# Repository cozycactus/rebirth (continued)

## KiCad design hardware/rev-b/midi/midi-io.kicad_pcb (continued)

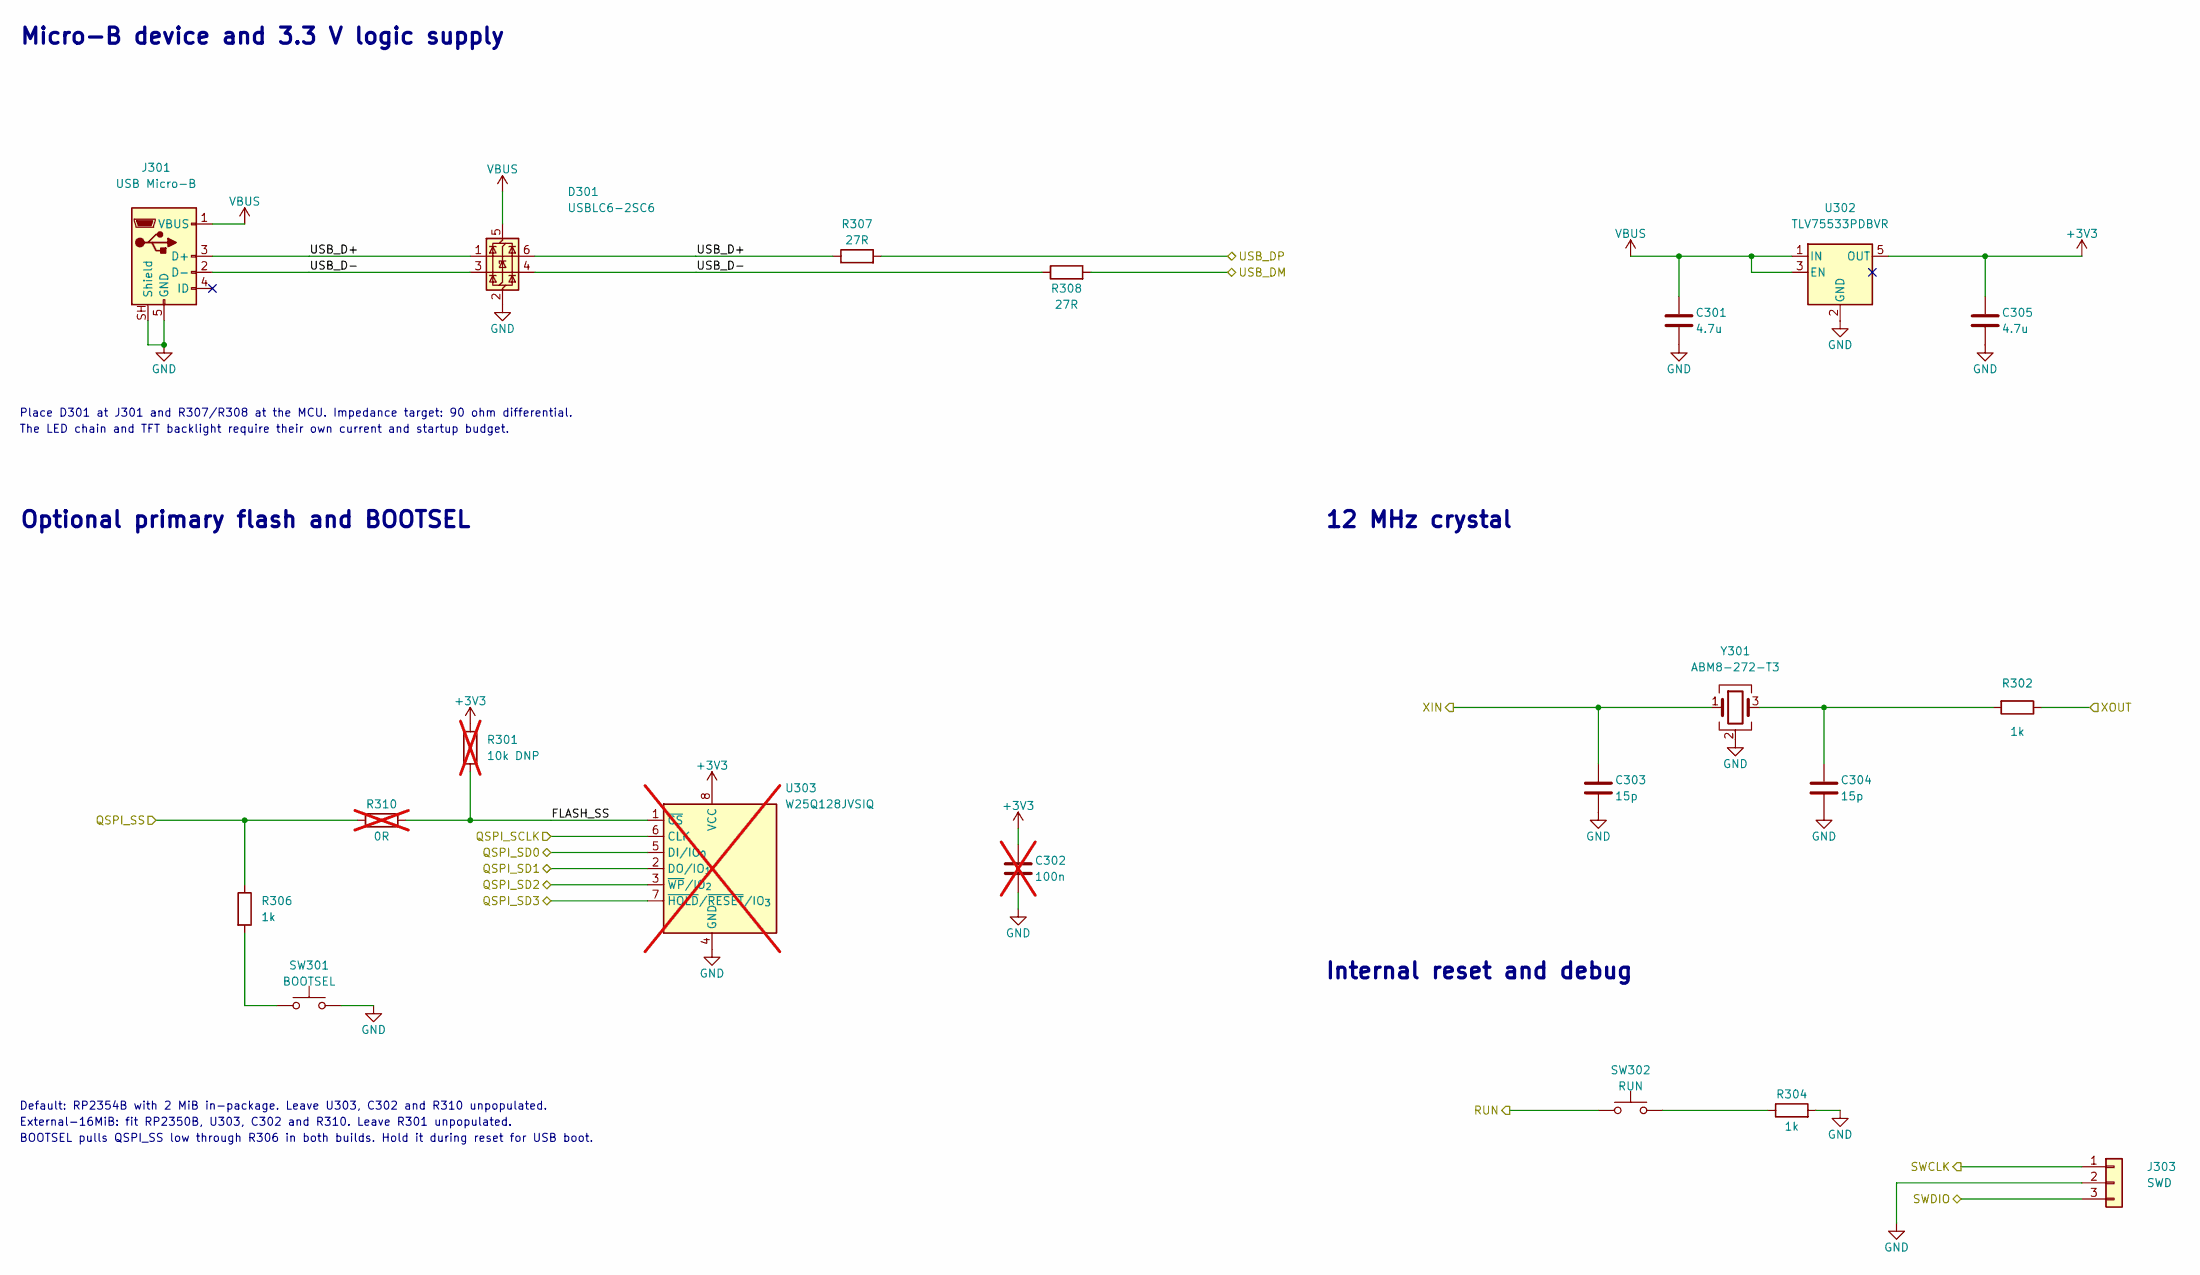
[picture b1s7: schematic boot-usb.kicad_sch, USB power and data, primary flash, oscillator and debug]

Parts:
C301, C305: 4.7u; C_0805_2012Metric; Rating 10 V X7R
C302: 100n; C_0402_1005Metric; not fitted
C303, C304: 15p; C_0402_1005Metric
D301: USBLC6-2SC6; SOT-23-6
J301: USB Micro-B; USB_Micro-B_Amphenol_10104110_Horizontal; MPN 10104110-0001LF
J303: SWD; PinHeader_1x03_P2.54mm_Vertical
R301: 10k DNP; R_0402_1005Metric; not fitted
R302, R304, R306: 1k; R_0402_1005Metric
R307, R308: 27R; R_0402_1005Metric
R310: 0R; R_0402_1005Metric; not fitted
SW301: BOOTSEL; SW_Push_1P1T_NO_Vertical_Wuerth_434133025816
SW302: RUN; SW_Push_1P1T_NO_Vertical_Wuerth_434133025816
U302: TLV75533PDBVR; SOT-23-5
U303: W25Q128JVSIQ; SOIC-8_5.3x5.3mm_P1.27mm; MPN W25Q128JVSIQ; not fitted
Y301: ABM8-272-T3; Crystal_SMD_3225-4Pin_3.2x2.5mm

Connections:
+3V3: C302.1, C305.1, R301.1, U302.5 (OUT), U303.8 (VCC); also elsewhere on the board
/QSPI_SCLK: U303.6 (CLK); also elsewhere on the board
/QSPI_SD0: U303.5 (DI/IO_{0}); also elsewhere on the board
/QSPI_SD1: U303.2 (DO/IO_{1}); also elsewhere on the board
/QSPI_SD2: U303.3 (~WP/IO_{2}); also elsewhere on the board
/QSPI_SD3: U303.7 (~HOLD/~RESET/IO_{3}); also elsewhere on the board
/QSPI_SS: R306.1, R310.1; also elsewhere on the board
/RUN: SW302.1; also elsewhere on the board
/SWCLK: J303.1; also elsewhere on the board
/SWDIO: J303.3; also elsewhere on the board
/USB, clock and storage/FLASH_SS: R301.2, R310.2, U303.1 (~CS)
/USB, clock and storage/USB_D+: D301.1 (I/O1), D301.6 (I/O1), J301.3 (D+), R307.1
/USB, clock and storage/USB_D-: D301.3 (I/O2), D301.4 (I/O2), J301.2 (D-), R308.1
/USB_DM: R308.2; also elsewhere on the board
/USB_DP: R307.2; also elsewhere on the board
/XIN: C303.1, Y301.1; also elsewhere on the board
/XOUT: R302.1; also elsewhere on the board
GND: C301.2, C302.2, C303.2, C304.2, C305.2, D301.2 (GND), J301.5 (GND), J301.SH (Shield), J303.2, R304.2, SW301.2, U302.2 (GND), U303.4 (GND), Y301.2 (G), Y301.4 (G); also elsewhere on the board
unnamed: C304.1, R302.2, Y301.3
unnamed: R304.1, SW302.2
unnamed: R306.2, SW301.1
VBUS: C301.1, D301.5 (VBUS), J301.1 (VBUS), U302.1 (IN), U302.3 (EN); also elsewhere on the board

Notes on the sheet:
Micro-B device and 3.3 V logic supply
Place D301 at J301 and R307/R308 at the MCU. Impedance target: 90 ohm differential.
The LED chain and TFT backlight require their own current and startup budget.
Optional primary flash and BOOTSEL
Default: RP2354B with 2 MiB in-package. Leave U303, C302 and R310 unpopulated.
External-16MiB: fit RP2350B, U303, C302 and R310. Leave R301 unpopulated.
BOOTSEL pulls QSPI_SS low through R306 in both builds. Hold it during reset for USB boot.
12 MHz crystal
Internal reset and debug

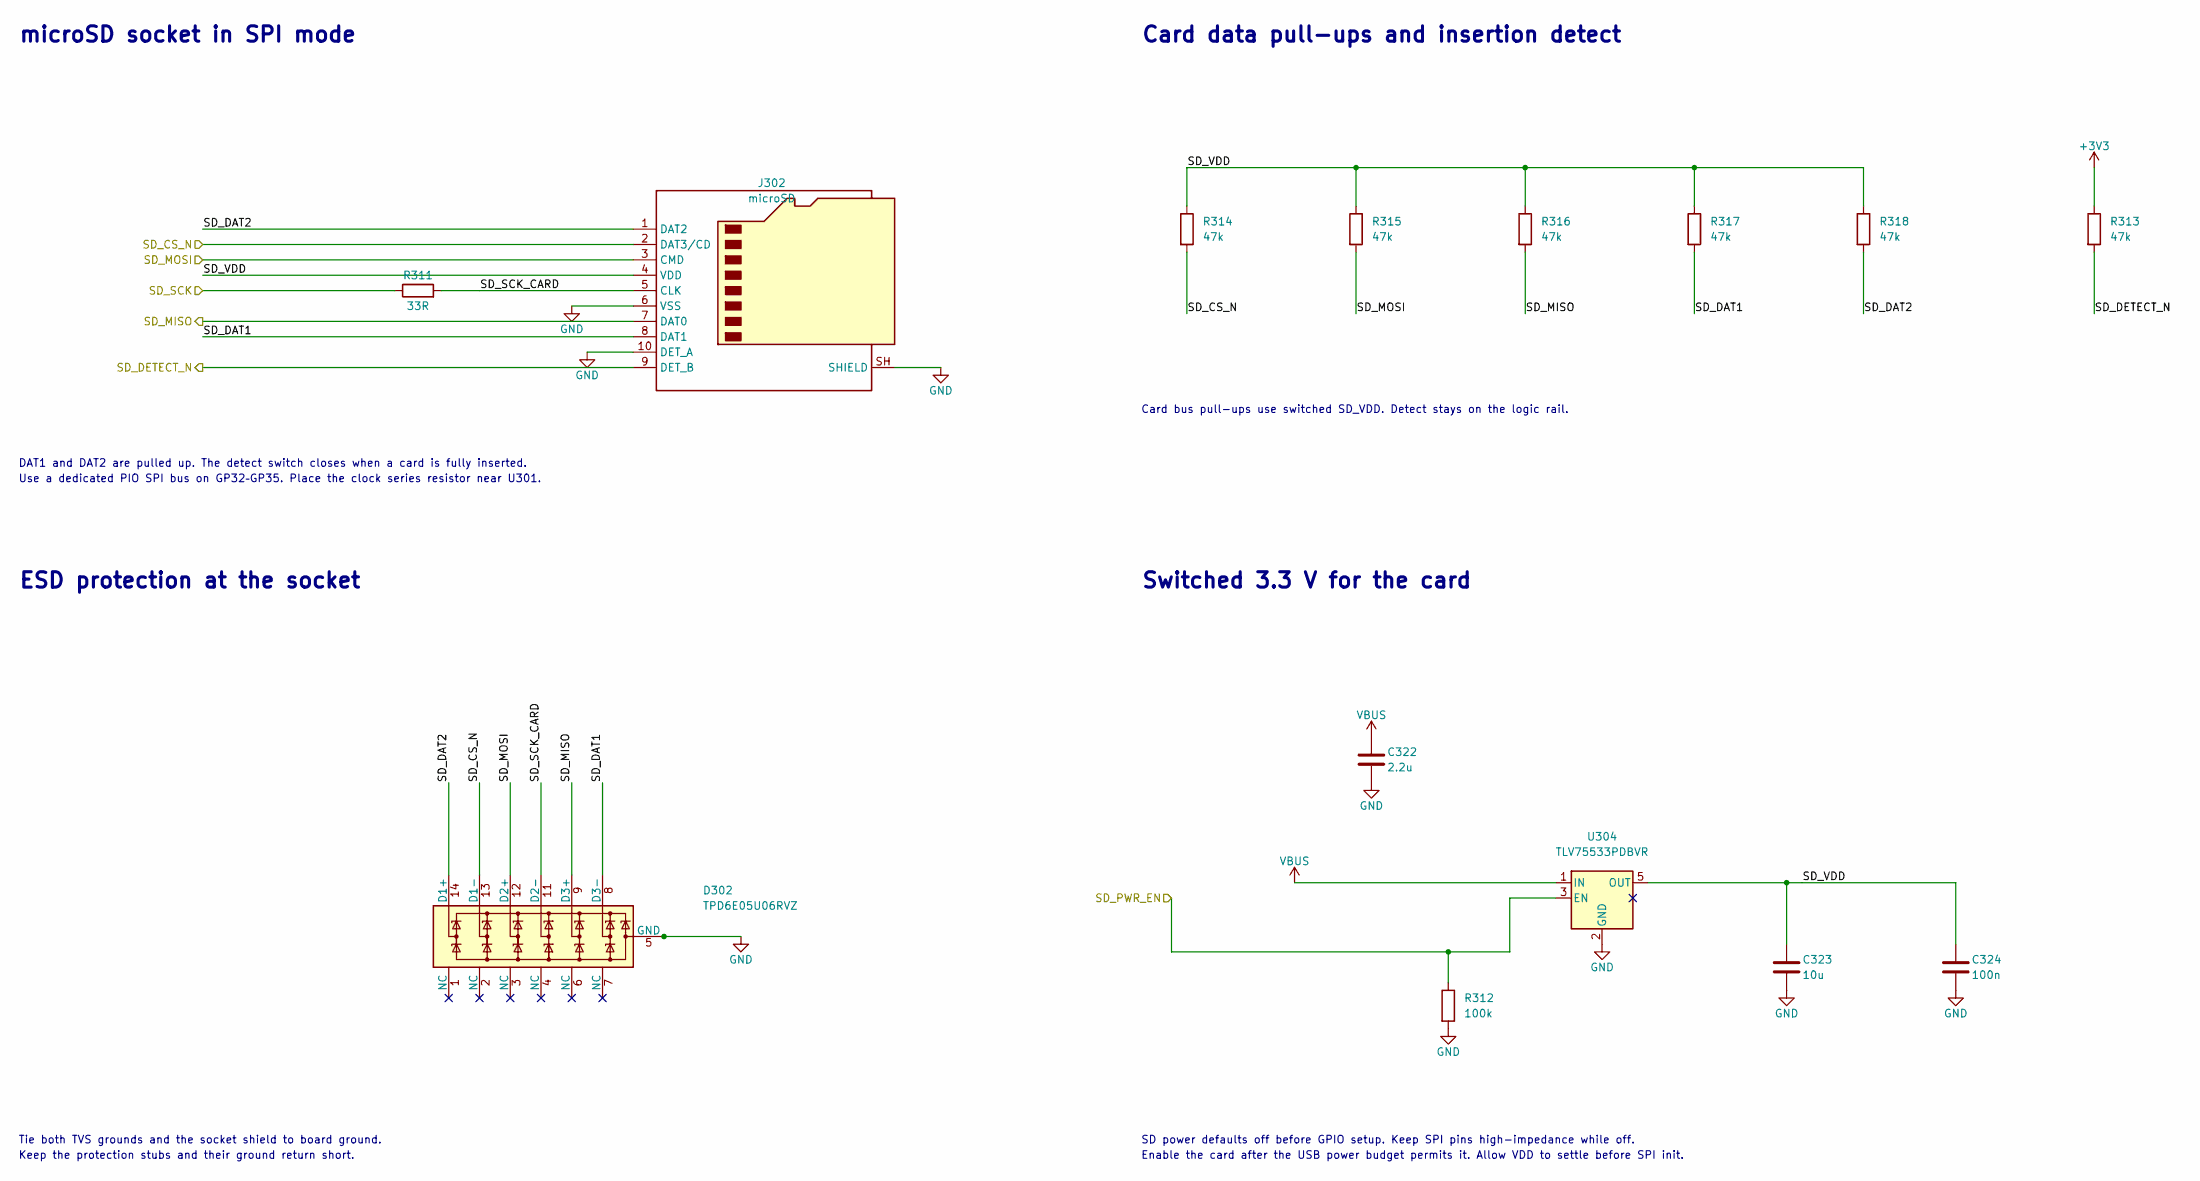
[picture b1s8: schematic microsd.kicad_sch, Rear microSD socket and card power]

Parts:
C322: 2.2u; C_0805_2012Metric; Rating 10 V X7R
C323: 10u; C_0805_2012Metric; Rating 10 V X7R
C324: 100n; C_0402_1005Metric; Rating 10 V X7R
D302: TPD6E05U06RVZ; Texas_R-PUSON-N14; MPN TPD6E05U06RVZR
J302: microSD; microSD_HC_Hirose_DM3AT-SF-PEJM5; MPN DM3AT-SF-PEJM5
R311: 33R; R_0402_1005Metric
R312: 100k; R_0402_1005Metric
R313, R314, R315, R316, R317, R318: 47k; R_0402_1005Metric
U304: TLV75533PDBVR; SOT-23-5

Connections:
+3V3: R313.1; also elsewhere on the board
/SD_CS_N: D302.13 (D1-), J302.2 (DAT3/CD), R314.2; also elsewhere on the board
/SD_DETECT_N: J302.9 (DET_B), R313.2; also elsewhere on the board
/SD_MISO: D302.9 (D3+), J302.7 (DAT0), R316.2; also elsewhere on the board
/SD_MOSI: D302.12 (D2+), J302.3 (CMD), R315.2; also elsewhere on the board
/SD_PWR_EN: R312.1, U304.3 (EN); also elsewhere on the board
/SD_SCK: R311.1; also elsewhere on the board
/microSD/SD_DAT1: D302.8 (D3-), J302.8 (DAT1), R317.2
/microSD/SD_DAT2: D302.14 (D1+), J302.1 (DAT2), R318.2
/microSD/SD_SCK_CARD: D302.11 (D2-), J302.5 (CLK), R311.2
/microSD/SD_VDD: C323.1, C324.1, J302.4 (VDD), R314.1, R315.1, R316.1, R317.1, R318.1, U304.5 (OUT)
GND: C322.2, C323.2, C324.2, D302.5 (GND), D302.10 (GND), J302.6 (VSS), J302.10 (DET_A), J302.SH (SHIELD), R312.2, U304.2 (GND); also elsewhere on the board
VBUS: C322.1, U304.1 (IN); also elsewhere on the board

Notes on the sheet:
microSD socket in SPI mode
DAT1 and DAT2 are pulled up. The detect switch closes when a card is fully inserted.
Use a dedicated PIO SPI bus on GP32–GP35. Place the clock series resistor near U301.
Card data pull-ups and insertion detect
Card bus pull-ups use switched SD_VDD. Detect stays on the logic rail.
ESD protection at the socket
Tie both TVS grounds and the socket shield to board ground.
Keep the protection stubs and their ground return short.
Switched 3.3 V for the card
SD power defaults off before GPIO setup. Keep SPI pins high-impedance while off.
Enable the card after the USB power budget permits it. Allow VDD to settle before SPI init.

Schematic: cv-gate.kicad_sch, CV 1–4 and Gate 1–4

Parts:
C501, C502, C504, C505, C507: 100n; C_0603_1608Metric
C506: 1u; C_0805_2012Metric
C511, C512, C513, C514: 1n C0G; C_0603_1608Metric
D501, D502, D503, D504, D505, D506, D507, D508: PESD5V0S1BA; D_SOD-323
J501, J502, J503, J504, J505, J506, J507, J508: 3.5mm TRS; Jack_3.5mm_CUI_SJ1-3533NG_Horizontal
R511, R512, R513, R514, R541, R542, R543, R544: 1k; R_0603_1608Metric
R515, R516, R517, R518, R531, R532, R533, R534, R551, R552, R553, R554: 100k; R_0603_1608Metric
R521, R522, R523, R524, R567, R568, R571, R572, R573: 10k; R_0603_1608Metric
R561, R562, R563, R564: 33R; R_0603_1608Metric
R565, R566, R569, R570: 47k; R_0603_1608Metric
U501, U502: MCP4822; SOIC-8_3.9x4.9mm_P1.27mm
U503: MCP6004; SOIC-14_3.9x8.7mm_P1.27mm
U504: SN74LVC8T245PWR; TSSOP-24_4.4x7.8mm_P0.65mm; MPN SN74LVC8T245PWR

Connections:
+3V3: C505.1, R567.1, R568.1, R573.1, U504.1 (V_{CCA}), U504.2 (DIR); also elsewhere on the board
/CV and Gate/CV1: D501.1 (A1), J501.T, R511.2, R521.2
/CV and Gate/CV1_DAC: R515.1, U501.8 (VA), U503.3 (+)
/CV and Gate/CV2: D502.1 (A1), J502.T, R512.2, R522.2
/CV and Gate/CV2_DAC: R516.1, U501.6 (VB), U503.5 (+)
/CV and Gate/CV3: D503.1 (A1), J503.T, R513.2, R523.2
/CV and Gate/CV3_DAC: R517.1, U502.8 (VA), U503.10 (+)
/CV and Gate/CV4: D504.1 (A1), J504.T, R514.2, R524.2
/CV and Gate/CV4_DAC: R518.1, U502.6 (VB), U503.12 (+)
/CV and Gate/DAC_CS1_N_T: R563.2, R571.2, U501.2 (~CS)
/CV and Gate/DAC_CS2_N_T: R564.2, R572.2, U502.2 (~CS)
/CV and Gate/DAC_MOSI_T: R562.2, R570.1, U501.4 (SDI), U502.4 (SDI)
/CV and Gate/DAC_SCK_T: R561.2, R569.1, U501.3 (SCK), U502.3 (SCK)
/CV and Gate/GATE1_BUF: R541.1, U504.17 (B5)
/CV and Gate/GATE1_OUT: D505.1 (A1), J505.T, R541.2, R551.1
/CV and Gate/GATE2_BUF: R542.1, U504.16 (B6)
/CV and Gate/GATE2_OUT: D506.1 (A1), J506.T, R542.2, R552.1
/CV and Gate/GATE3_BUF: R543.1, U504.15 (B7)
/CV and Gate/GATE3_OUT: D507.1 (A1), J507.T, R543.2, R553.1
/CV and Gate/GATE4_BUF: R544.1, U504.14 (B8)
/CV and Gate/GATE4_OUT: D508.1 (A1), J508.T, R544.2, R554.1
/CV_ENABLE_N: R573.2, U504.22 (~OE); also elsewhere on the board
/DAC_CS1_N: R567.2, U504.5 (A3); also elsewhere on the board
/DAC_CS2_N: R568.2, U504.6 (A4); also elsewhere on the board
/DAC_MOSI: R566.1, U504.4 (A2); also elsewhere on the board
/DAC_SCK: R565.1, U504.3 (A1); also elsewhere on the board
/GATE1: R531.1, U504.7 (A5); also elsewhere on the board
/GATE2: R532.1, U504.8 (A6); also elsewhere on the board
/GATE3: R533.1, U504.9 (A7); also elsewhere on the board
/GATE4: R534.1, U504.10 (A8); also elsewhere on the board
GND: C501.2, C502.2, C504.2, C505.2, C506.2, C507.2, D501.2 (A2), D502.2 (A2), D503.2 (A2), D504.2 (A2), D505.2 (A2), D506.2 (A2), D507.2 (A2), D508.2 (A2), J501.S, J502.S, J503.S, J504.S, J505.S, J506.S, J507.S, J508.S, R515.2, R516.2, R517.2, R518.2, R531.2, R532.2, R533.2, R534.2, R551.2, R552.2, R553.2, R554.2, R565.2, R566.2, R569.2, R570.2, U501.5 (~LDAC), U501.7 (Vss), U502.5 (~LDAC), U502.7 (Vss), U503.11 (V-), U504.11 (GND), U504.12 (GND), U504.13 (GND); also elsewhere on the board
unnamed: C511.2, R511.1, U503.1
unnamed: C512.2, R512.1, U503.7
unnamed: C513.2, R513.1, U503.8
unnamed: C514.2, R514.1, U503.14
unnamed: C511.1, R521.1, U503.2 (-)
unnamed: C512.1, R522.1, U503.6 (-)
unnamed: C513.1, R523.1, U503.9 (-)
unnamed: C514.1, R524.1, U503.13 (-)
unnamed: R561.1, U504.21 (B1)
unnamed: R562.1, U504.20 (B2)
unnamed: R563.1, U504.19 (B3)
unnamed: R564.1, U504.18 (B4)
VBUS: C501.1, C502.1, C504.1, C506.1, C507.1, R571.1, R572.1, U501.1 (Vdd), U502.1 (Vdd), U503.4 (V+), U504.23 (V_{CCB}), U504.24 (V_{CCB}); also elsewhere on the board

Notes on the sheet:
CV/Gate level translation
DIR is high. A takes 3.3 V logic, B drives the VBUS domain.
OE stays high until firmware sets chip selects high and the four gates low.
Place the 33 ohm SPI series resistors close to U504.
Reset levels
Four pitch outputs, 1 V/octave
MCP4822 at gain 2x on VBUS. Nominal 1 mV/LSB at the jack.
At 4.096 V full scale, allow supply and buffer headroom under load.
Measure slope and offset at the jacks with the connected synth.
CV 1
CV 2
CV 3
CV 4
MCP6004 buffers. R511–R514 are inside the DC feedback loop.
C511–C514 close local feedback at high frequency.
D501–D508 are rear-jack TVS diodes.
Four active-high Gate outputs
GATE 1
GATE 2
GATE 3
GATE 4
The jacks are held low while OE is high.
Use the tip and sleeve of a TS cable. Ring is open.
Check the high Gate level and CV settling under load.

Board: 2 copper layers, 187 parts (0 on the bottom side), 114 nets, no tracks yet.

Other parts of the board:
H1, H2, H3, H4, H5, H6, H7: MountingHole_3.2mm_M3_Pad_Via
J1101: IDC 2x13, wire order; IDC-Header_2x13_P2.54mm_Horizontal

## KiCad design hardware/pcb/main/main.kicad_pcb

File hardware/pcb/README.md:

# PCB: main board and panel board

Two KiCad 10 projects, one per board, generated from the schematic
(`hardware/schematic/`, its README first):

| Board | Project | Size | Contents |
| --- | --- | --- | --- |
| Panel board | `panel/panel.kicad_pro` | 248 x 251 mm | 8x8 pads, 8 SCENE, 8 MUTE, PLAY (81 MX switches), 82 SK6812MINI-E, 80 BAT54J, 16 step buttons and LEDs, 5 MCP23017, encoders, OLED socket, LED data buffer, cable header J1201 |
| Main board | `main/main.kicad_pro` | 244 x 57.5 mm | Raspberry Pi Pico, LED-rail switch U201, MIDI OUT/IN, 2 x MCP4822 + MCP6004, gate buffer, 8 jacks, 2 DIN-5, cable header J1101 |

The two boards are joined by a 26-wire IDC ribbon, J1101 pin n to J1201 pin n.

## Decisions (owner, 2026-11-16)

| Question | Decision |
| --- | --- |
| One board or two | Two: panel board under the top plate, main board on the case floor at the rear wall |
| Copper layers | 2 on both boards, 1.6 mm FR4, 1 oz |
| Fab and assembly | JLCPCB, their SMT assembly with LCSC parts; through-hole parts soldered by hand |
| Pads | MX-type switches soldered to the panel board, translucent 17 mm keycaps through windows in the 2 mm aluminium top plate, board on 15 mm standoffs |
| LED rail enable | JP201: EN = +3V3 as designed, GPIO 7 by moving a solder jumper |
| Jack protection | 5 V TVS on all eight jacks |
| Case height | 28 mm at the front, 50 mm at the rear (mockup: 20/45 mm) |

The board plan was reviewed independently (Codex, DeepSeek, Grok; Gemini could not run) before
layout. What came out of it is in the schematic README (decisions 12-14) and below.

## Regenerating

The boards are generated, like the schematic. With KiCad 10 installed:

```bash
python3 hardware/schematic/gen/build.py --check          # schematics of all three projects
PY=/Applications/KiCad/KiCad.app/Contents/Frameworks/Python.framework/Versions/Current/bin/python3
$PY hardware/pcb/gen/build_pcb.py panel place            # footprints, outline, holes, regular routing
$PY hardware/pcb/gen/build_pcb.py panel maze             # grid router for the rest (panel)
$PY hardware/pcb/gen/build_pcb.py panel finish           # GND pours, stitching vias, DRC + parity
```

For the main board: `place`, then
`FREEROUTING_JAR=/path/to/freerouting-2.4.1.jar $PY hardware/pcb/gen/build_pcb.py main route`,
then `maze` and `finish`. `place` overwrites the board file; `route` hands the unrouted
connections to Freerouting (GND is left out, it is poured); `maze` joins what is still open
with the grid router in `gen/maze.py`; `finish` adds the GND pours on both layers and stitching
vias, joins GND islands, refills and runs `kicad-cli pcb drc --schematic-parity`. Run `finish`
again until the DRC summary it prints stops changing (two or three times). The panel takes
about half an hour, the main board a few minutes. Placement is
in `gen/panel.py` and `gen/mainboard.py`, the panel geometry in `gen/geometry.py` (from the
Blender mockup `hardware/panel/build_panel.py`).

## Mechanics (case frame: x to the right, y toward the rear wall, z up)

The Blender model `hardware/panel/build_internals.py` shows all of this and animates it
(scene "Sequencer Internals": the plate and caps lift off, the lid with the panel board opens).

- **Stack under the top plate.** Plate 2 mm; panel board top 15 mm below the plate's underside on
  M3 standoffs. Cherry MX: housing top 11.6 mm, stem top 15.2 mm above the board (MX2A datasheet:
  18.5 mm total with 3.3 mm pins); a DSA-height cap reaches ~20 mm, ~3 mm above the plate, and
  goes ~1 mm below the plate surface at full travel. Plate windows: caps + 0.8 mm. Change the
  standoffs with the keycap profile.
- **Case height** 28 mm at the front, 50 mm at the rear (tilt 4.7 deg). At the front edge the
  panel board's underside is ~12 mm above the 3 mm floor; at the rear ~2 mm stay between the
  DIN sockets and the panel board.
- **Panel board holes** (17 x M3, plated, on GND) sit around the grid block, between the step
  groups and beside the top strip; none inside the 8x8 grid (the caps leave no room for a
  standoff). Centre deflection of the 1.6 mm board between the supports is a few tenths of a
  millimetre for a 10 N press; if the grid feels soft, add a non-conductive support from the
  case floor under the grid centre. The aluminium plate is grounded through the standoffs only
  if it is bare or chromated at the screw faces (anodising insulates): use toothed washers or
  a ground tab and check < 1 ohm from the plate to GND.
- **Top strip.** EC11 encoders need a ~30 mm shaft from the board (the KiCad footprint name
  says H20mm; the pinout is the same) and pass the plate without a nut; the OLED module sits on
  ~11 mm spacers so the glass is just under the 57 x 29 mm window, plugged into the 7-pin
  socket J601 at its top edge (check the module's header position and pin order before
  ordering, or join them with a short cable). BEAT (D982) lights through a light pipe; the
  step buttons are tall 6 x 6 tactiles (~15 mm) with caps, the step LEDs stand on long legs up
  to Ø4 mm plate holes (sleeve the legs: the plate is on GND).
- **Main board** on 5 mm standoffs (7 x M3, plated, on GND, one beside the DIN sockets to take
  their up-to-5-kgf plug force). The Pico's edge is flush with the board's rear edge, so its
  micro-USB receptacle sits ~2 mm inside the 3 mm rear wall: thin the wall around the USB
  opening to ~1 mm, or use a short panel-mount extension. The jacks (CUI SJ1-3513N, no thread)
  and the DIN-5 sockets (SDS-50J) have their faces at the board's rear edge.
- **Cable.** Both headers are right angle and open toward the front: J1201 under the panel
  board above J1101 at the main board's front edge; the ribbon leaves both plugs forward and
  folds back on itself (~100 mm). Keyed headers and keyed IDC sockets, stripe = pin 1 on both
  ends.

## Cable J1101 - J1201 (wire n = pin n)

| Pin | Net | Pin | Net |
| --- | --- | --- | --- |
| 1 | +5V_LED | 2 | +5V_LED |
| 3 | GND | 4 | LED_DATA |
| 5 | GND | 6 | OLED_SCK |
| 7 | GND | 8 | OLED_MOSI |
| 9 | OLED_DC | 10 | OLED_CS_N |
| 11 | OLED_RST_N | 12 | PLAY_N |
| 13 | +3V3 | 14 | +3V3 |
| 15 | GND | 16 | I2C_SCL |
| 17 | GND | 18 | I2C_SDA |
| 19 | ENC1_A | 20 | ENC1_B |
| 21 | ENC1_SW_N | 22 | ENC2_A |
| 23 | ENC2_B | 24 | ENC2_SW_N |
| 25 | GND | 26 | GND |

A ribbon crimped the wrong way round joins pin n to pin 27 - n: +5V_LED meets GND (U201 limits
it to ~0.3 A) and +3V3 meets +3V3; no rail reaches another rail. Ring pin 1 to pin 1 before
the first power-up anyway. Up to 306 mA flows on the two +5V_LED wires and back on seven GND
wires (well within a 28 AWG ribbon and IDC contacts).

## Panel board

- **Sides.** Every SMD part is on the bottom (B), so the board needs one SMT pass; through-hole
  parts (81 MX switches, 16 tactiles, 16 step LEDs, 2 encoders, OLED socket J601, cable header
  J1201) are hand-soldered, the switches from the top. The SK6812MINI-E are reverse mounted:
  KiCad's `LED_SK6812MINI-E_3.2x2.8mm_P1.5mm_ReverseMount` placed on B.Cu, the lens in the
  board cutout under the MX LED window, 5.08 mm from the switch centre on the side away from
  the switch pins. Their pads are 0.2-0.25 mm from that cutout; `panel.kicad_dru` allows 0.2 mm
  for them only (JLCPCB routes to 0.2 mm), the rest of the board keeps 0.25 mm. JLCPCB lists
  C5149201 as Standard PCBA only; check the reel's pin 1 against the footprint (schematic
  README, notes for the PCB step) and the bottom-side rotation in the CPL before ordering.
- **Key cell** (19.5 mm pitch, KiCad coordinates relative to the switch centre, +y toward the
  front): MX footprint origin at (+2.54, -5.08); LED at (0, +5.08); its 100 nF at (+4.6, +5.8),
  vertical; BAT54J at (+4.9, -7.6), anode toward switch pin 1. Copper: ROW line on B.Cu through
  switch pin 2 at y -2.54, COL line on F.Cu at x +7.0 with the diode cathode on a via, LED chain
  on B.Cu above the LED pads, +5V_LED bus (0.6 mm) on B.Cu at y +8.6, two GND vias per cell.
- **+5V_LED**: J1201 pins 1-2 -> 1 mm F.Cu under the header body (clear of both pin rows, so
  the cable pins can leave downward on either layer) -> via -> C984 (470 uF) -> 1 mm feed along
  the top of the grid -> 1 mm spine on F.Cu down the right side (x = 95.5) -> a via onto every
  row bus and the mute bus.
- **Expanders.** Step row: U701 (0x20) and U703 (0x24) at the left margin, U702 (0x21, LEDs) at
  the right; key scanner U801 (0x22) and U802 (0x23) at the right margin next to the ROW line
  ends. Each expander's RESET pull-up sits right of its pin 18.
- **Step row buses.** Between the step LEDs (with their 470 R underneath) and the step buttons
  is a channel ~8 mm high. B.Cu carries U702's 16 LED lines to the 470 R, F.Cu the 16 button
  lines from U701/U703, 0.5 mm pitch, both drawn by `gen/panel.py`. On both expanders one pin
  column comes out in the reverse order of the row; the LED lines solve it by leaving U702 on
  both sides (GPB7 takes F.Cu round H12), the button lines by a diagonal of vias on U701's
  right column and a B.Cu loop under the chip to a staircase of vias for its left column. They
  come down between D701 and D702. U901 (LED data buffer) and C984 sit next to J1201, so the chain starts and the LED
  current enters at the same corner.
- **Routing.** The key grid, the LED supply and the step-row buses are drawn by `gen/panel.py`;
  the rest by a grid
  router (`gen/maze.py`: A* on a 0.2 mm grid on both layers, KiCad's clearances grown into the
  grid, no vias in SMD pads or next to holes). A connection that finds no way gets a trial path
  that may cross other signal nets at a cost; only the nets it crosses are ripped up and routed
  again after it, and the best of up to eight rounds is kept. Freerouting made no progress on this board (182 of 324
  connections still open after two passes and 30 minutes). Many long runs cross the grid
  diagonally: electrically fine, tidier by hand later if wanted.

## Main board

- **Left:** the Pico U301 on 8.5 mm sockets, its USB end 0.5 mm inside the rear edge; the
  source terminations R1101-R1105 and R561-R564 right at its GPIO pins (R1106 for LED_DATA on
  the other side); U201 (LED-rail switch), C201/C202, JP201 and TP201 beside its VBUS pin.
- **J1101** in front of the Pico, opening to the front edge, so the LED supply and its return
  stay at the Pico end of the board.
- **Middle:** MIDI OUT behind J401, MIDI IN (H11L1, DIP-6) behind J402.
- **Right:** gate buffer U504 between the gate jacks, op-amp U503 between the CV jacks, the two
  DACs in front of it; the 1 k / 10 k / 1 nF network and the TVS of each channel in front of
  its jack. The DAC SPI lines (~170 mm, 33 R at the source) run along the front of the board.
- All SMD parts on the top (one SMT pass). JLCPCB's Standard PCBA asks for at least 70 mm on
  the short side: order the 57.5 mm board with edge rails, or use Economic PCBA if every part
  qualifies.
- **Routing:** Freerouting, then `gen/maze.py` for the few connections it leaves (with rip-up of
  the nets that wall a pad in). GND poured on both layers, stitched.

## Fabrication (JLCPCB)

- 2 layers, FR4 1.6 mm, 1 oz copper, ENIG preferred (fine reverse-mount LED pads; HASL works).
- Rules: routed at 0.2 mm track/space; the DRC holds 0.15 mm (JLCPCB minimum 0.127 mm), vias
  0.6/0.3 mm (power 0.8/0.4 mm), copper 0.25 mm from the outline (0.2 mm for the LED pads at
  their cutouts), hole to hole 0.5 mm.
- Fiducials: three per assembly side (panel: bottom, main: top). Mounting holes are plated
  and on GND. Reference designators of the dense parts are on the fab layers, so the
  silkscreen stays readable; the assembly drawing comes from F.Fab/B.Fab.
- Not prepared here: BOM with LCSC numbers and the CPL (the schematic has no MPNs yet).

## Verification (2026-11-16, KiCad 10.0.7)

| Check | Main board | Panel board |
| --- | --- | --- |
| `kicad-cli pcb drc --schematic-parity --severity-all` against the rules above | 0 violations, 0 unconnected, 0 parity issues | 0 violations, 0 unconnected, 0 parity issues |
| Footprints / nets on the board = schematic | 109 / 91 | 437 / 307 |
| Copper connectivity (kicad-happy `analyze_pcb.py --full`, union-find over pads, tracks, vias and fills) | every net one island | every net one island |
| kicad-happy `cross_analysis.py` | 2 info (MIDI DIN pins without ESD parts) | 0 findings |

Schematics: `python3 hardware/schematic/gen/build.py --check` gives 0 problems and 0 ERC
violations for all three projects (380 / 91 / 307 nets) and 26 of 26 cable pins matched; the
generated sheets are unchanged by the PCB work. Copper pictures: `renders/panel_copper.jpg`,
`renders/main_copper.jpg` (F.Cu pour drawn over B.Cu).

kicad-happy findings that stay, and why:

- Main, PM-002 "courtyard overhangs the board edge": J401/J402 (0.5 mm), J501-J508 (4 mm) and
  U301 (1.06 mm). On purpose: the jack and DIN faces and the Pico's USB end sit at the rear edge.
- Main, CC-002: two short MIDI_TX segments (under 3 mm together) at 0.15 mm, where Freerouting
  necked down between pins; above JLCPCB's 0.127 mm, and the line carries ~5 mA. Everything else
  is 0.2 mm or wider.
- Both, TE-001 test-point coverage (2 of 88 nets on main, none on the panel): bring-up uses the
  Pico pins, the jacks and the cable header; TP201 and TP301 are the only test points.
- Main schematic, CG-AUD "J402 has no ground pin": MIDI IN leaves pin 2 open by the MIDI spec.
- Main schematic, PU-001 "U201 EN without pull-up": EN has R203 to GND and JP201 to +3V3 (or
  GPIO 7), as designed.
- Both schematics, DS-001 / SS-001: no datasheets folder and no MPNs, so the analyzer's checks
  are consistency checks only, not checks against the parts' datasheets.

Not done here: Gerbers, drill files, BOM with LCSC numbers and the CPL; the EMC, thermal and
SPICE passes of kicad-happy; a readable-schematic lint of the regenerated sheets (it timed out
after 600 s; the sheets were checked by eye on renders). Freerouting results vary from run to
run, so a regenerated main board is not identical to the committed one; the panel's routing
comes out the same every time.

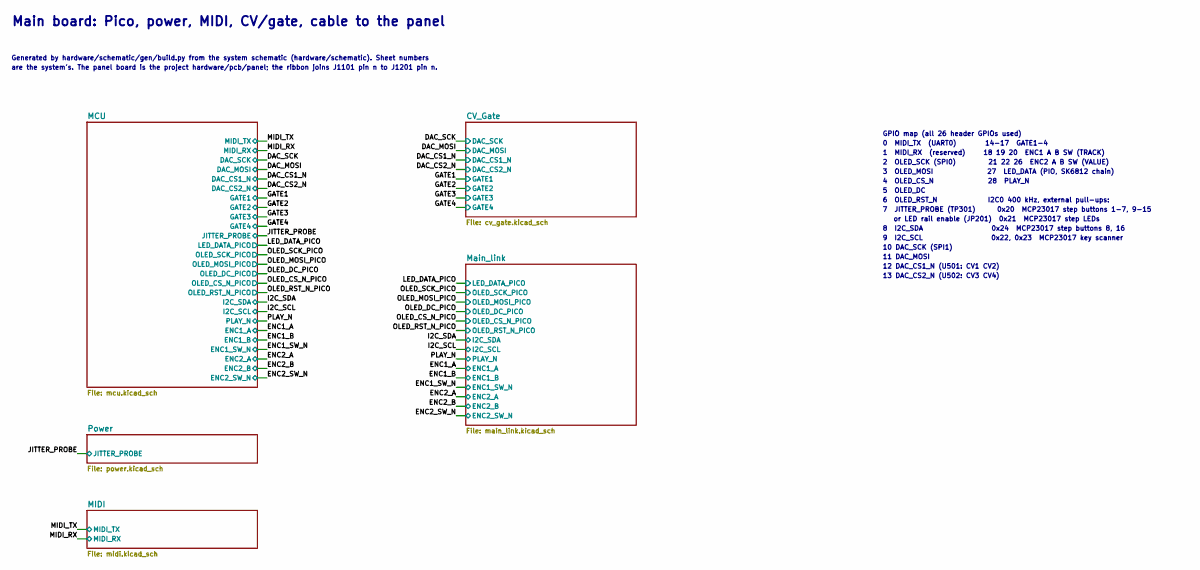
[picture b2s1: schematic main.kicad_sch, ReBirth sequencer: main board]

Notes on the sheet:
Main board: Pico, power, MIDI, CV/gate, cable to the panel
Generated by hardware/schematic/gen/build.py from the system schematic (hardware/schematic). Sheet numbers
are the system's. The panel board is the project hardware/pcb/panel; the ribbon joins J1101 pin n to J1201 pin n.
GPIO map (all 26 header GPIOs used)
0 MIDI_TX (UART0) 14-17 GATE1-4
1 MIDI_RX (reserved) 18 19 20 ENC1 A B SW (TRACK)
2 OLED_SCK (SPI0) 21 22 26 ENC2 A B SW (VALUE)
3 OLED_MOSI 27 LED_DATA (PIO, SK6812 chain)
4 OLED_CS_N 28 PLAY_N
5 OLED_DC
6 OLED_RST_N I2C0 400 kHz, external pull-ups:
7 JITTER_PROBE (TP301) 0x20 MCP23017 step buttons 1-7, 9-15
or LED rail enable (JP201) 0x21 MCP23017 step LEDs
8 I2C_SDA 0x24 MCP23017 step buttons 8, 16
9 I2C_SCL 0x22, 0x23 MCP23017 key scanner
10 DAC_SCK (SPI1)
11 DAC_MOSI
12 DAC_CS1_N (U501: CV1 CV2)
13 DAC_CS2_N (U502: CV3 CV4)

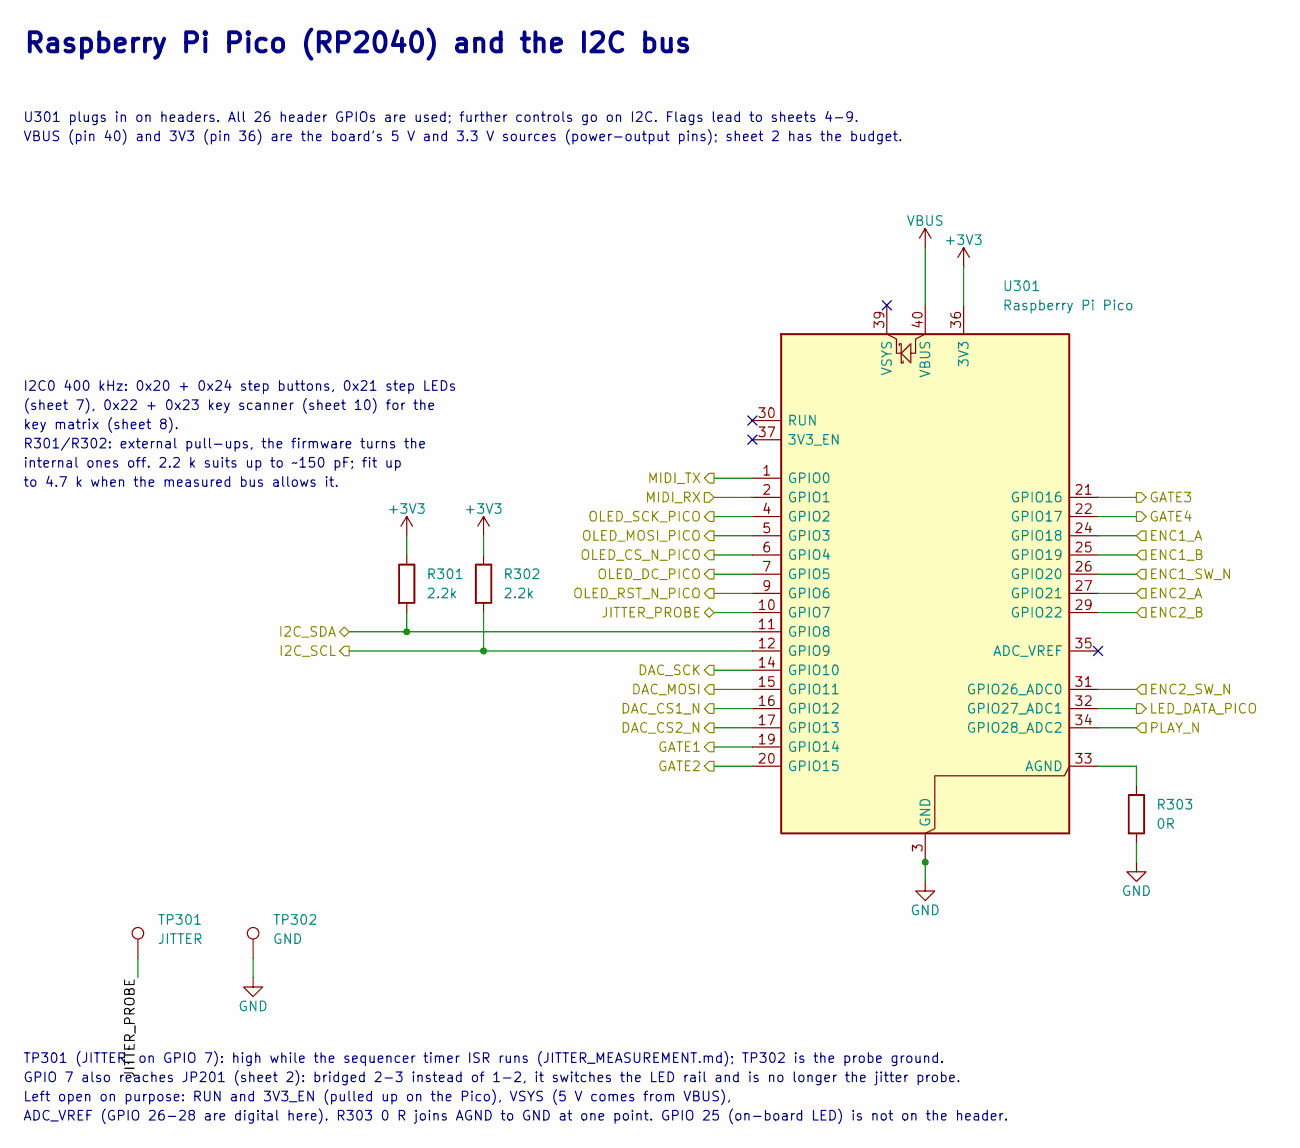
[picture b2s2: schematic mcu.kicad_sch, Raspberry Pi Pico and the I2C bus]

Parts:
R301, R302: 2.2k; R_0603_1608Metric
R303: 0R; R_0603_1608Metric
TP301: JITTER; TestPoint_Pad_D1.5mm
TP302: GND; TestPoint_Pad_D1.5mm
U301: Raspberry Pi Pico; RaspberryPi_Pico_Common_THT

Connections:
+3V3: R301.1, R302.1, U301.36 (3V3); also elsewhere on the board
/DAC_CS1_N: U301.16 (GPIO12); also elsewhere on the board
/DAC_CS2_N: U301.17 (GPIO13); also elsewhere on the board
/DAC_MOSI: U301.15 (GPIO11); also elsewhere on the board
/DAC_SCK: U301.14 (GPIO10); also elsewhere on the board
/ENC1_A: U301.24 (GPIO18); also elsewhere on the board
/ENC1_B: U301.25 (GPIO19); also elsewhere on the board
/ENC1_SW_N: U301.26 (GPIO20); also elsewhere on the board
/ENC2_A: U301.27 (GPIO21); also elsewhere on the board
/ENC2_B: U301.29 (GPIO22); also elsewhere on the board
/ENC2_SW_N: U301.31 (GPIO26_ADC0); also elsewhere on the board
/GATE1: U301.19 (GPIO14); also elsewhere on the board
/GATE2: U301.20 (GPIO15); also elsewhere on the board
/GATE3: U301.21 (GPIO16); also elsewhere on the board
/GATE4: U301.22 (GPIO17); also elsewhere on the board
/I2C_SCL: R302.2, U301.12 (GPIO9); also elsewhere on the board
/I2C_SDA: R301.2, U301.11 (GPIO8); also elsewhere on the board
/JITTER_PROBE: TP301.1, U301.10 (GPIO7); also elsewhere on the board
/LED_DATA_PICO: U301.32 (GPIO27_ADC1); also elsewhere on the board
/MIDI_RX: U301.2 (GPIO1); also elsewhere on the board
/MIDI_TX: U301.1 (GPIO0); also elsewhere on the board
/OLED_CS_N_PICO: U301.6 (GPIO4); also elsewhere on the board
/OLED_DC_PICO: U301.7 (GPIO5); also elsewhere on the board
/OLED_MOSI_PICO: U301.5 (GPIO3); also elsewhere on the board
/OLED_RST_N_PICO: U301.9 (GPIO6); also elsewhere on the board
/OLED_SCK_PICO: U301.4 (GPIO2); also elsewhere on the board
/PLAY_N: U301.34 (GPIO28_ADC2); also elsewhere on the board
GND: R303.2, TP302.1, U301.3 (GND), U301.8 (GND), U301.13 (GND), U301.18 (GND), U301.23 (GND), U301.28 (GND), U301.38 (GND); also elsewhere on the board
unnamed: R303.1, U301.33 (AGND)
VBUS: U301.40 (VBUS); also elsewhere on the board

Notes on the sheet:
Raspberry Pi Pico (RP2040) and the I2C bus
U301 plugs in on headers. All 26 header GPIOs are used; further controls go on I2C. Flags lead to sheets 4-9.
VBUS (pin 40) and 3V3 (pin 36) are the board's 5 V and 3.3 V sources (power-output pins); sheet 2 has the budget.
I2C0 400 kHz: 0x20 + 0x24 step buttons, 0x21 step LEDs
(sheet 7), 0x22 + 0x23 key scanner (sheet 10) for the
key matrix (sheet 8).
R301/R302: external pull-ups, the firmware turns the
internal ones off. 2.2 k suits up to ~150 pF; fit up
to 4.7 k when the measured bus allows it.
TP301 (JITTER, on GPIO 7): high while the sequencer timer ISR runs (JITTER_MEASUREMENT.md); TP302 is the probe ground.
GPIO 7 also reaches JP201 (sheet 2): bridged 2-3 instead of 1-2, it switches the LED rail and is no longer the jitter probe.
Left open on purpose: RUN and 3V3_EN (pulled up on the Pico), VSYS (5 V comes from VBUS),
ADC_VREF (GPIO 26-28 are digital here). R303 0 R joins AGND to GND at one point. GPIO 25 (on-board LED) is not on the header.

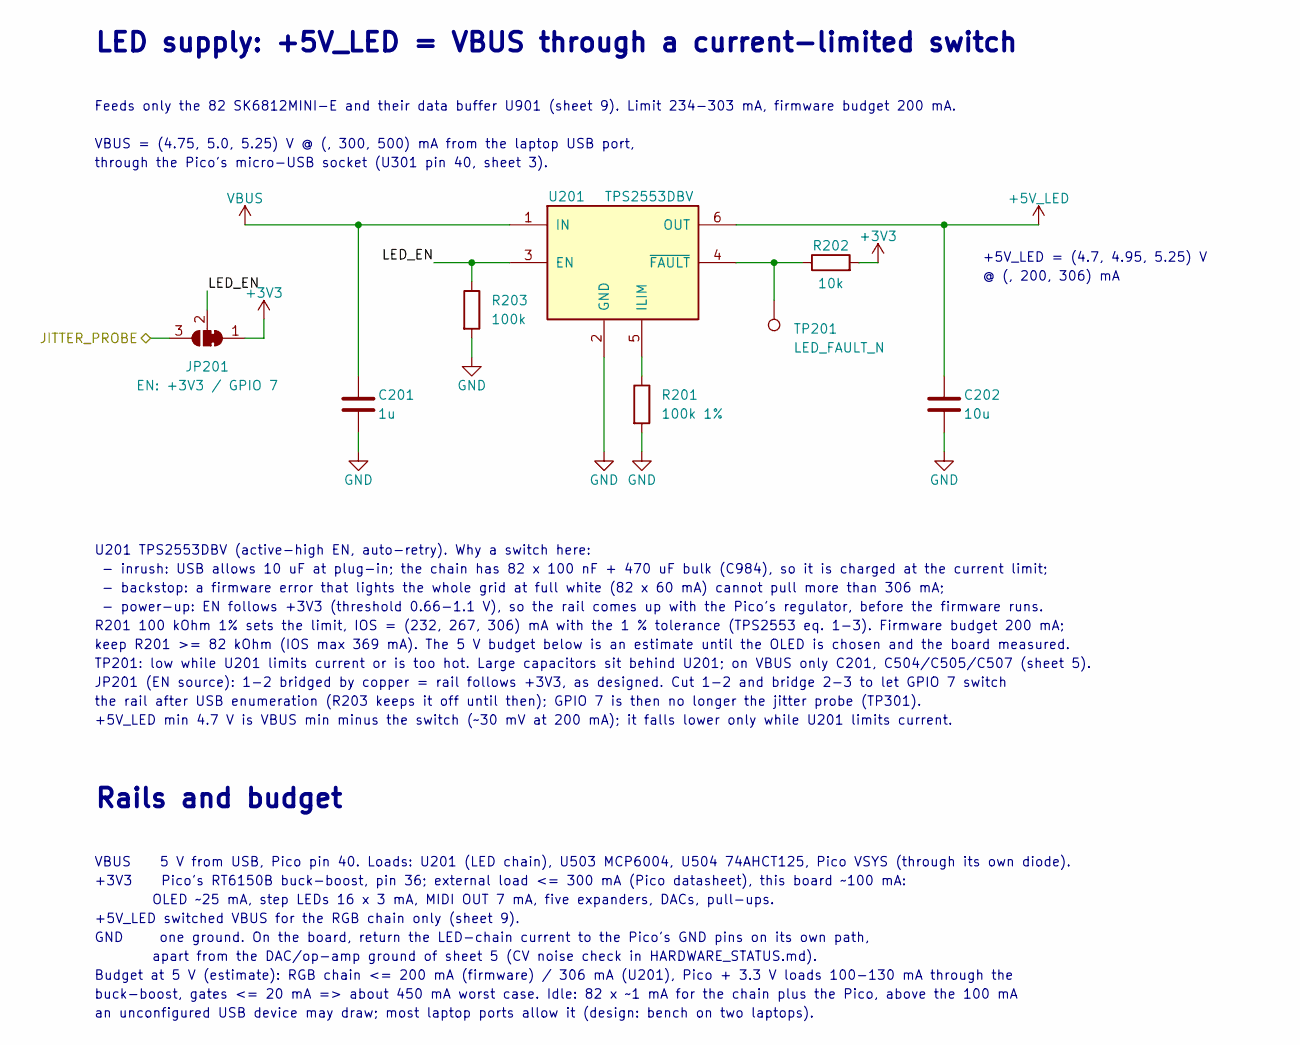
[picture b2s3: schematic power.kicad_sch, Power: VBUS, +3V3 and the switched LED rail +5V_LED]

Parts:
C201: 1u; C_0805_2012Metric
C202: 10u; C_0805_2012Metric
JP201: EN: +3V3 / GPIO 7; SolderJumper-3_P1.3mm_Bridged12_RoundedPad1.0x1.5mm_NumberL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
R201: 100k 1%; R_0603_1608Metric
R202: 10k; R_0603_1608Metric
R203: 100k; R_0603_1608Metric
TP201: LED_FAULT_N; TestPoint_Pad_D1.5mm
U201: TPS2553DBV; SOT-23-6

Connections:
+3V3: JP201.1 (A), R202.2; also elsewhere on the board
+5V_LED: C202.1, U201.6 (OUT); also elsewhere on the board
/JITTER_PROBE: JP201.3 (B); also elsewhere on the board
/Power/LED_EN: JP201.2 (C), R203.1, U201.3 (EN)
GND: C201.2, C202.2, R201.2, R203.2, U201.2 (GND); also elsewhere on the board
unnamed: R201.1, U201.5 (ILIM)
unnamed: R202.1, TP201.1, U201.4 (~FAULT)
VBUS: C201.1, U201.1 (IN); also elsewhere on the board

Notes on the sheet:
LED supply: +5V_LED = VBUS through a current-limited switch
Feeds only the 82 SK6812MINI-E and their data buffer U901 (sheet 9). Limit 234-303 mA, firmware budget 200 mA.
VBUS = (4.75, 5.0, 5.25) V @ (, 300, 500) mA from the laptop USB port,
through the Pico's micro-USB socket (U301 pin 40, sheet 3).
+5V_LED = (4.7, 4.95, 5.25) V
@ (, 200, 306) mA
U201 TPS2553DBV (active-high EN, auto-retry). Why a switch here:
- inrush: USB allows 10 uF at plug-in; the chain has 82 x 100 nF + 470 uF bulk (C984), so it is charged at the current limit;
- backstop: a firmware error that lights the whole grid at full white (82 x 60 mA) cannot pull more than 306 mA;
- power-up: EN follows +3V3 (threshold 0.66-1.1 V), so the rail comes up with the Pico's regulator, before the firmware runs.
R201 100 kOhm 1% sets the limit, IOS = (232, 267, 306) mA with the 1 % tolerance (TPS2553 eq. 1-3). Firmware budget 200 mA;
keep R201 >= 82 kOhm (IOS max 369 mA). The 5 V budget below is an estimate until the OLED is chosen and the board measured.
TP201: low while U201 limits current or is too hot. Large capacitors sit behind U201; on VBUS only C201, C504/C505/C507 (sheet 5).
JP201 (EN source): 1-2 bridged by copper = rail follows +3V3, as designed. Cut 1-2 and bridge 2-3 to let GPIO 7 switch
the rail after USB enumeration (R203 keeps it off until then); GPIO 7 is then no longer the jitter probe (TP301).
+5V_LED min 4.7 V is VBUS min minus the switch (~30 mV at 200 mA); it falls lower only while U201 limits current.
Rails and budget
VBUS 5 V from USB, Pico pin 40. Loads: U201 (LED chain), U503 MCP6004, U504 74AHCT125, Pico VSYS (through its own diode).
+3V3 Pico's RT6150B buck-boost, pin 36; external load <= 300 mA (Pico datasheet), this board ~100 mA:
OLED ~25 mA, step LEDs 16 x 3 mA, MIDI OUT 7 mA, five expanders, DACs, pull-ups.
+5V_LED switched VBUS for the RGB chain only (sheet 9).
GND one ground. On the board, return the LED-chain current to the Pico's GND pins on its own path,
apart from the DAC/op-amp ground of sheet 5 (CV noise check in HARDWARE_STATUS.md).
Budget at 5 V (estimate): RGB chain <= 200 mA (firmware) / 306 mA (U201), Pico + 3.3 V loads 100-130 mA through the
buck-boost, gates <= 20 mA => about 450 mA worst case. Idle: 82 x ~1 mA for the chain plus the Pico, above the 100 mA
an unconfigured USB device may draw; most laptop ports allow it (design: bench on two laptops).

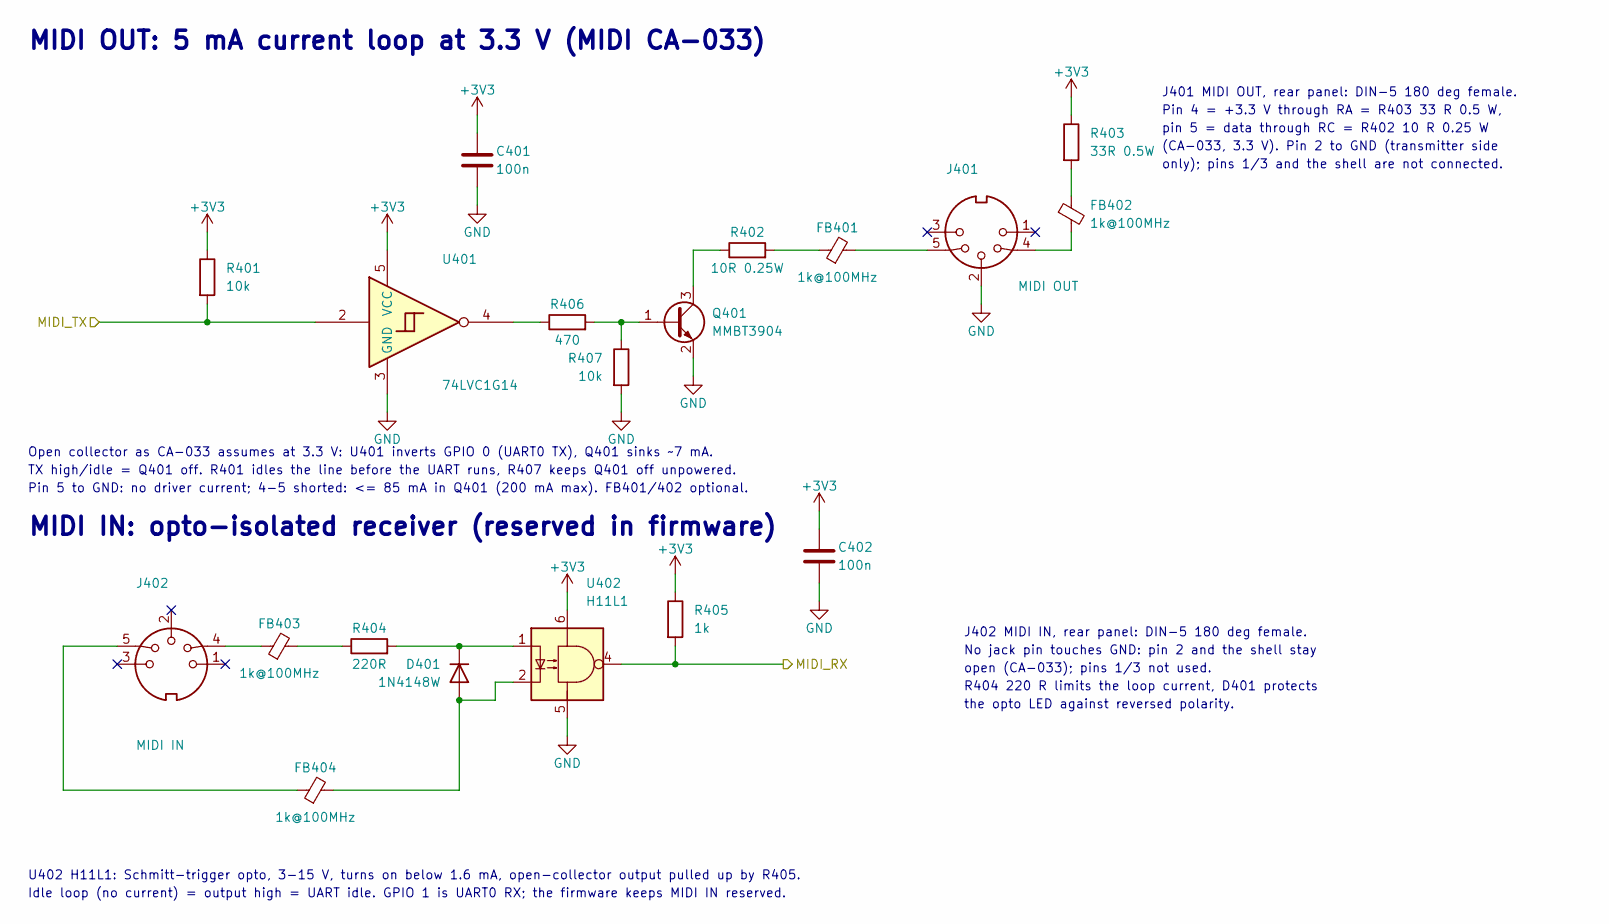
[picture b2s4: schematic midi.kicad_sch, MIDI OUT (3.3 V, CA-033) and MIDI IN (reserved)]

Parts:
C401, C402: 100n; C_0603_1608Metric
D401: 1N4148W; D_SOD-123
FB401, FB402, FB403, FB404: 1k@100MHz; L_0603_1608Metric
J401: MIDI OUT; DIN-5_180deg_SameSky_SDS-50J_Horizontal
J402: MIDI IN; DIN-5_180deg_SameSky_SDS-50J_Horizontal
Q401: MMBT3904; SOT-23
R401, R407: 10k; R_0603_1608Metric
R402: 10R 0.25W; R_1206_3216Metric
R403: 33R 0.5W; R_1210_3225Metric
R404: 220R; R_0603_1608Metric
R405: 1k; R_0603_1608Metric
R406: 470; R_0603_1608Metric
U401: 74LVC1G14; SOT-23-5
U402: H11L1; DIP-6_W7.62mm

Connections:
+3V3: C401.1, C402.1, R401.1, R403.1, R405.1, U401.5 (VCC), U402.6; also elsewhere on the board
/MIDI_RX: R405.2, U402.4; also elsewhere on the board
/MIDI_TX: R401.2, U401.2; also elsewhere on the board
GND: C401.2, C402.2, J401.2, Q401.2 (E), R407.2, U401.3 (GND), U402.5; also elsewhere on the board
unnamed: D401.2 (A), FB404.2, U402.2
unnamed: D401.1 (K), R404.2, U402.1
unnamed: FB401.1, R402.2
unnamed: FB401.2, J401.5
unnamed: FB402.1, R403.2
unnamed: FB402.2, J401.4
unnamed: FB403.1, J402.4
unnamed: FB403.2, R404.1
unnamed: FB404.1, J402.5
unnamed: Q401.1 (B), R406.2, R407.1
unnamed: Q401.3 (C), R402.1
unnamed: R406.1, U401.4

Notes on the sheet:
MIDI OUT: 5 mA current loop at 3.3 V (MIDI CA-033)
J401 MIDI OUT, rear panel: DIN-5 180 deg female.
Pin 4 = +3.3 V through RA = R403 33 R 0.5 W,
pin 5 = data through RC = R402 10 R 0.25 W
(CA-033, 3.3 V). Pin 2 to GND (transmitter side
only); pins 1/3 and the shell are not connected.
Open collector as CA-033 assumes at 3.3 V: U401 inverts GPIO 0 (UART0 TX), Q401 sinks ~7 mA.
TX high/idle = Q401 off. R401 idles the line before the UART runs, R407 keeps Q401 off unpowered.
Pin 5 to GND: no driver current; 4-5 shorted: <= 85 mA in Q401 (200 mA max). FB401/402 optional.
MIDI IN: opto-isolated receiver (reserved in firmware)
J402 MIDI IN, rear panel: DIN-5 180 deg female.
No jack pin touches GND: pin 2 and the shell stay
open (CA-033); pins 1/3 not used.
R404 220 R limits the loop current, D401 protects
the opto LED against reversed polarity.
U402 H11L1: Schmitt-trigger opto, 3-15 V, turns on below 1.6 mA, open-collector output pulled up by R405.
Idle loop (no current) = output high = UART idle. GPIO 1 is UART0 RX; the firmware keeps MIDI IN reserved.
